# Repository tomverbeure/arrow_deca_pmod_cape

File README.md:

# Arrow DECA PMOD Cape

Simple PMOD extension board for Arrow DECA connector.

**Status: not yet finished. This needs a 5V to 3V3 LDO to feed the PMOD rails, instead
of connecting straight to the 3V3 pin (which very likely doesn't have enough
power.)**

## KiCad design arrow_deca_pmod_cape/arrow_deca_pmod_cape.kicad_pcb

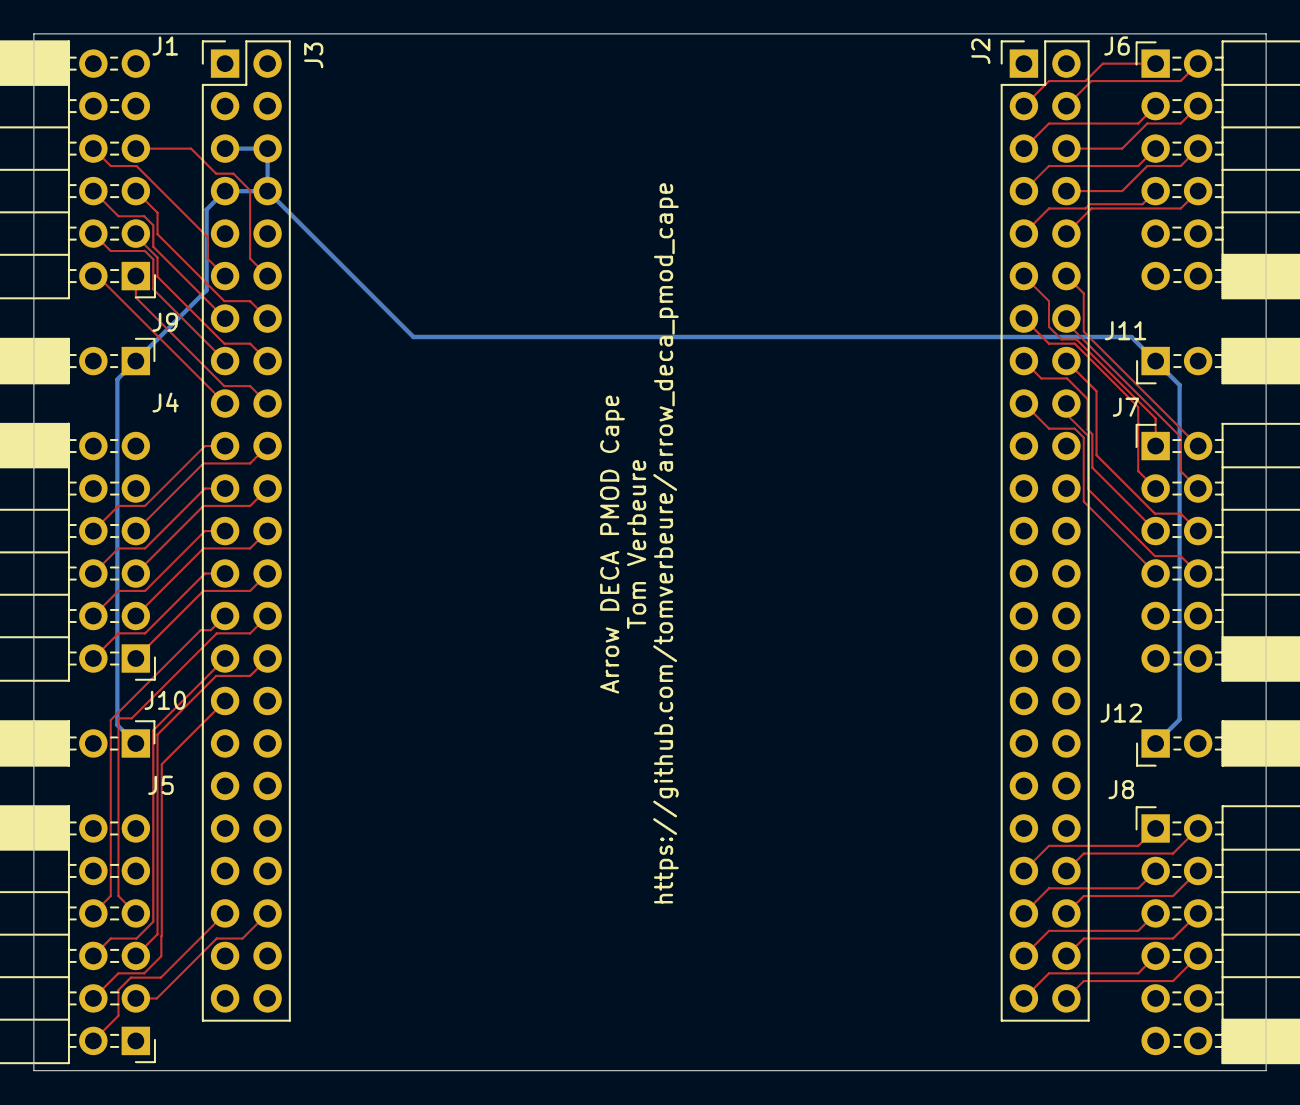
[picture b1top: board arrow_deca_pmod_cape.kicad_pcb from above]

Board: 4 copper layers, 73.7 x 62.0 mm, 12 parts (0 on the bottom side), 50 nets.

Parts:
J1: PMOD_A; PMOD_Female_Horizontal
J2: P8_Male; PinHeader_2x23_P2.54mm_Vertical
J3: P9_Male; PinHeader_2x23_P2.54mm_Vertical
J4: PMOD_B; PMOD_Female_Horizontal
J5: PMOD_C; PMOD_Female_Horizontal
J6: PMOD_D; PMOD_Female_Horizontal
J7: PMOD_E; PMOD_Female_Horizontal
J8: PMOD_F; PMOD_Female_Horizontal
J9, J10, J11, J12: Conn_02x01; PinSocket_2x01_P2.54mm_Horizontal

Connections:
+3V3: J1.6, J1.12, J3.3, J3.4, J4.6, J4.12, J5.6, J5.12, J6.6, J6.12, J7.6, J7.12, J8.6, J8.12
+5V: J3.5, J3.6, J3.7, J3.8, J9.1, J10.1, J11.1, J12.1
/GPIO0_D0: J2.3, J6.1
/GPIO0_D1: J2.4, J6.7
/GPIO0_D2: J2.5, J6.2
/GPIO0_D3: J2.6, J6.8
/GPIO0_D4: J2.7, J6.3
/GPIO0_D5: J2.8, J6.9
/GPIO0_D6: J2.9, J6.4
/GPIO0_D7: J2.10, J6.10
/GPIO0_D8: J2.11, J7.1
/GPIO0_D9: J2.12, J7.7
/GPIO0_D10: J2.13, J7.2
/GPIO0_D11: J2.14, J7.8
/GPIO0_D12: J2.15, J7.3
/GPIO0_D13: J2.16, J7.9
/GPIO0_D14: J2.17, J7.4
/GPIO0_D15: J2.18, J7.10
/GPIO0_D36: J2.39, J8.1
/GPIO0_D37: J2.40, J8.7
/GPIO0_D38: J2.41, J8.2
/GPIO0_D39: J2.42, J8.8
/GPIO0_D40: J2.43, J8.3
/GPIO0_D41: J2.44, J8.9
/GPIO0_D42: J2.45, J8.4
/GPIO0_D43: J2.46, J8.10
/GPIO1_D0: J1.10, J3.11
/GPIO1_D1: J1.4, J3.12
/GPIO1_D2: J1.9, J3.13
/GPIO1_D3: J1.3, J3.14
/GPIO1_D4: J1.8, J3.15
/GPIO1_D5: J1.2, J3.16
/GPIO1_D6: J1.7, J3.17
/GPIO1_D7: J1.1, J3.18
/GPIO1_D8: J3.19, J4.10
/GPIO1_D9: J3.20, J4.4
/GPIO1_D10: J3.21, J4.9
/GPIO1_D11: J3.22, J4.3
/GPIO1_D12: J3.23, J4.8
/GPIO1_D13: J3.24, J4.2
/GPIO1_D14: J3.25, J4.7
/GPIO1_D15: J3.26, J4.1
/GPIO1_D16: J3.27, J5.10
/GPIO1_D17: J3.28, J5.4
/GPIO1_D18: J3.29, J5.9
/GPIO1_D19: J3.30, J5.3
/GPIO1_D20: J3.31, J5.8
/GPIO1_D21: J3.41, J5.7
/GPIO1_D22: J3.42, J5.2
GND: J1.5, J1.11, J2.1, J2.2, J3.1, J3.2, J3.43, J3.44, J3.45, J3.46, J4.5, J4.11, J5.5, J5.11, J6.5, J6.11, J7.5, J7.11, J8.5, J8.11, J9.2, J10.2, J11.2, J12.2

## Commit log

2021-06-16 WIP.
2021-07-05 Move labels.
2021-07-05 Add README.md.
2021-07-05 Add 3D pic.
